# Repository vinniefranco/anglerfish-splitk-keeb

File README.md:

# Anglerfish Keyboard

Anglerfish, is a split keyboard with 3x5 column staggered keys, two thumb keys, and a trackball.

The Trackpoint can be placed on either side, and the PCB is a reversible design.

---

---

### Models
You can find all the step files for the case [here](assets/models)

### Electronic Components 
[Build of materials](assets/bom.md)

### Default Firmware Keymap

---

### Build Guide
Soon...

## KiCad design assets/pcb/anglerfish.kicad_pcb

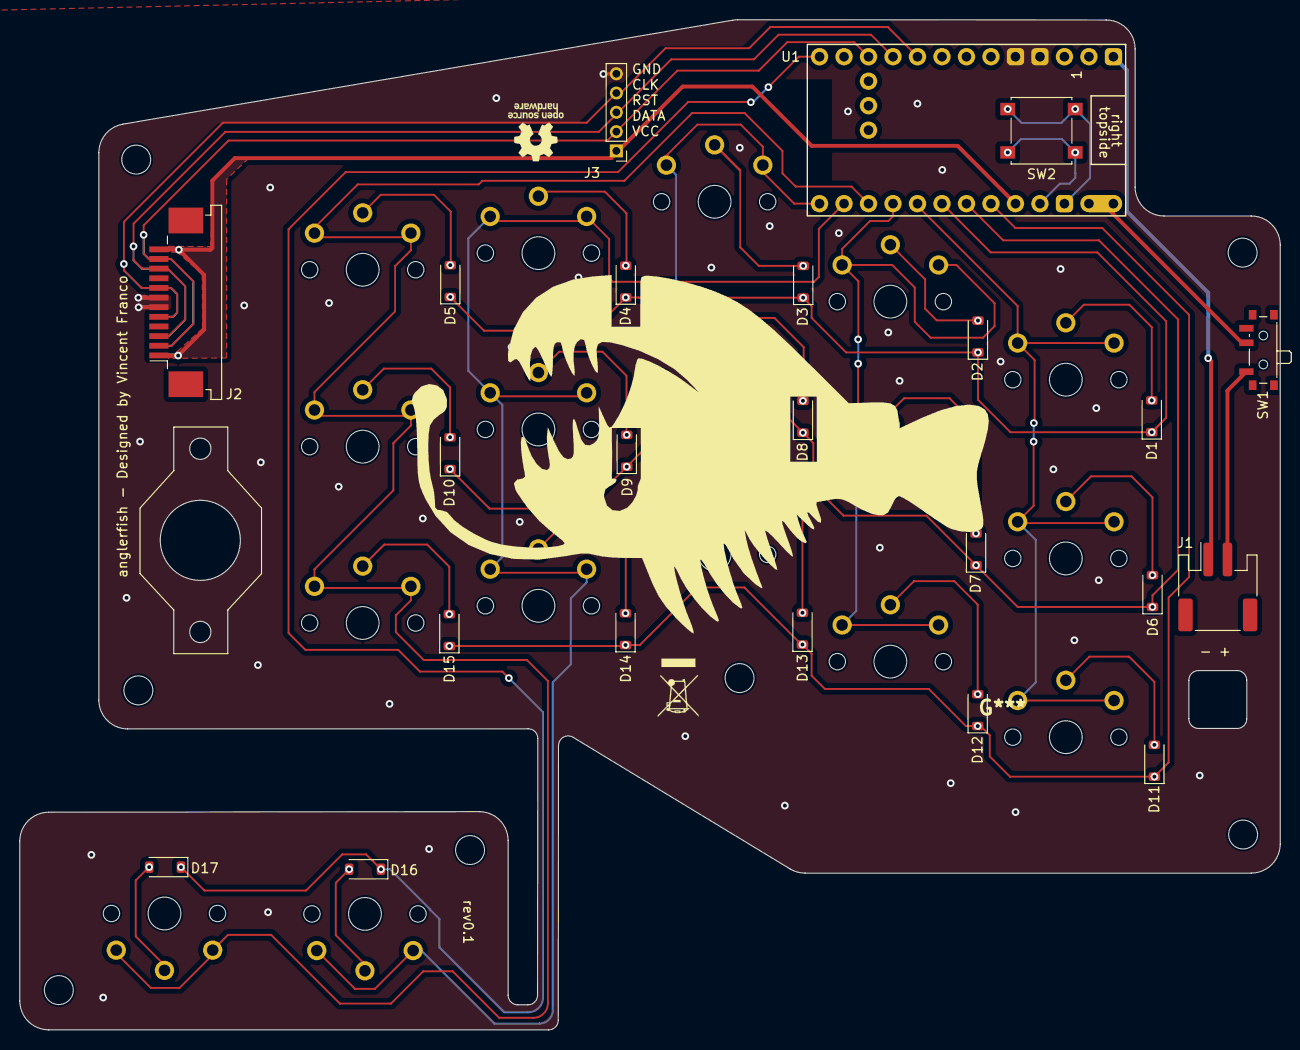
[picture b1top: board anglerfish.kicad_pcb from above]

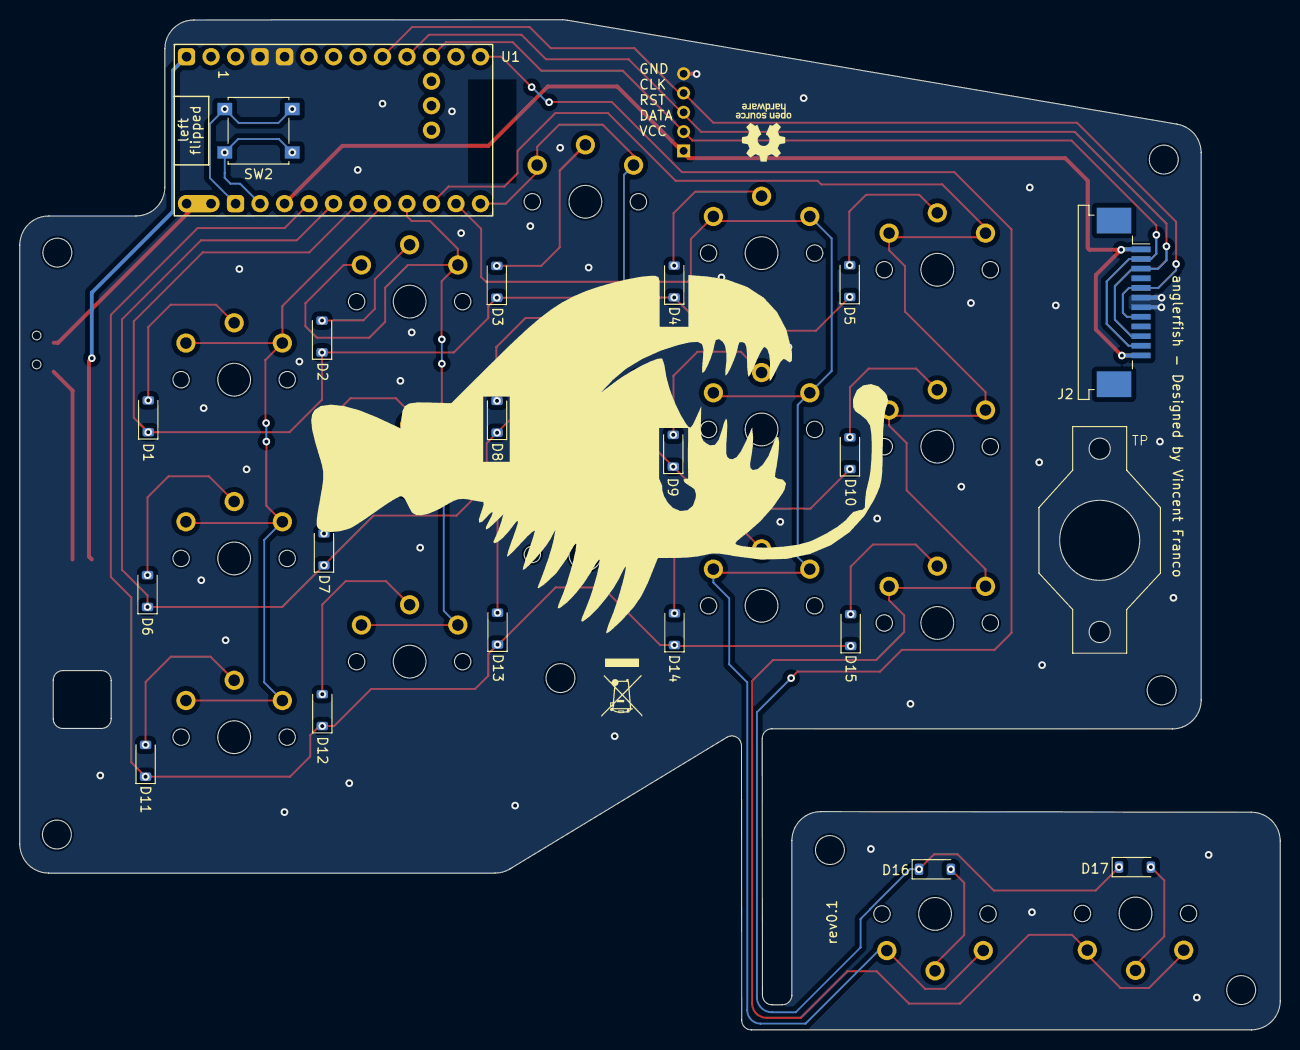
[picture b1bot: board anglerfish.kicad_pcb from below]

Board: 2 copper layers, 130.7 x 104.8 mm, 67 parts (19 on the bottom side), 35 nets.

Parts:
CH1, CH2, CH3, CH4, CH5, CH6, CH7, CH8, CH9, CH10, CH11, CH12, CH13, CH14, CH15, CH16, CH17: kailh choc; SW_choc_Reversible_1u
D1, D1#2, D2, D2#2, D3, D3#2, D4, D4#2, D5, D5#2, D6, D6#2, D7, D7#2, D8, D8#2, D9, D9#2, D10, D10#2, D11, D11#2, D12, D12#2, D13, D13#2, D14, D14#2, D15, D15#2, D16, D16#2, D17, D17#2: 1N4148; D_SOD-123
H1, H1#2, H2, H3, H4, H5, H6: MountingHole; MountingHole_3mm
J1: JST_PH_S2B-PH-SM4-TB; JST_PH_S2B-PH-SM4-TB_1x02-1MP_P2.00mm_Horizontal
J2, J2#2: TE_1-84952-2; TE_1-84952-2_1x12-1MP_P1.0mm_Horizontal
J3: Conn_01x05_Socket; PinHeader_1x05_P2.00mm_Vertical
SW1: SW_SPST_PCM12; SW_SPDT_PCM12
SW2, SW2#2: SW_SPST_B3S-1000
TP: Trackpoint
U1: supermini nrf / nice nano v2; nice_nano_AH_USBup

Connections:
BATTN: J1.1, U1.28 (GND)
BATTP: J1.2, SW1.1 (A), SW1.2 (B), U1.13 (BAT+), U1.29 (BAT+)
COL0: CH1.1, CH6.1, CH11.1, U1.20 (P1.15-LF)
COL1: CH2.1, CH7.1, CH12.1, U1.21 (P1.13-LF)
COL2: CH3.1, CH8.1, CH13.1, U1.24 (P0.09-LF)
COL3: CH4.1, CH9.1, CH14.1, CH16.1, U1.23 (P0-10-LF)
COL4: CH5.1, CH10.1, CH15.1, CH17.1, U1.22 (P1.11-LF)
unnamed: CH1.2, D1.2 (A), D1#2.2 (A)
unnamed: CH2.2, D2.2 (A), D2#2.2 (A)
unnamed: CH3.2, D3.2 (A), D3#2.2 (A)
unnamed: CH4.2, D4.2 (A), D4#2.2 (A)
unnamed: CH5.2, D5.2 (A), D5#2.2 (A)
unnamed: CH6.2, D6.2 (A), D6#2.2 (A)
unnamed: CH7.2, D7.2 (A), D7#2.2 (A)
unnamed: CH8.2, D8.2 (A), D8#2.2 (A)
unnamed: CH9.2, D9.2 (A), D9#2.2 (A)
unnamed: CH10.2, D10.2 (A), D10#2.2 (A)
unnamed: CH11.2, D11.2 (A), D11#2.2 (A)
unnamed: CH12.2, D12.2 (A), D12#2.2 (A)
unnamed: CH13.2, D13.2 (A), D13#2.2 (A)
unnamed: CH14.2, D14.2 (A), D14#2.2 (A)
unnamed: CH15.2, D15.2 (A), D15#2.2 (A)
unnamed: CH16.2, D16.2 (A), D16#2.2 (A)
unnamed: CH17.2, D17.2 (A), D17#2.2 (A)
ROW0: D1.1 (K), D1#2.1 (K), D2.1 (K), D2#2.1 (K), D3.1 (K), D3#2.1 (K), D4.1 (K), D4#2.1 (K), D5.1 (K), D5#2.1 (K), U1.19 (P0.02-LF)
ROW1: D6.1 (K), D6#2.1 (K), D7.1 (K), D7#2.1 (K), D8.1 (K), D8#2.1 (K), D9.1 (K), D9#2.1 (K), D10.1 (K), D10#2.1 (K), U1.18 (P0.29-LF)
ROW2: D11.1 (K), D11#2.1 (K), D12.1 (K), D12#2.1 (K), D13.1 (K), D13#2.1 (K), D14.1 (K), D14#2.1 (K), D15.1 (K), D15#2.1 (K), U1.17 (P0.31-LF)
ROW3: D16.1 (K), D16#2.1 (K), D17.1 (K), D17#2.1 (K), U1.12 (P1.06-LF)
RSTG: SW2.2 (B), SW2#2.2 (B), U1.14 (GND)
RSTR: SW2.1 (A), SW2#2.1 (A), U1.15 (RST)
TPCLK: J2.5, J2.8, J2#2.5, J2#2.8, J3.4, U1.8 (P0.24)
TPDATA: J2.2, J2.11, J2#2.2, J2#2.11, J3.2, U1.10 (P0.11)
TPGND: J2.6, J2.7, J2#2.6, J2#2.7, J3.5, U1.3 (GND), U1.4 (GND)
TPRST: J2.3, J2.10, J2#2.3, J2#2.10, J3.3, U1.9 (P1.00)
TPVCC: J2.1, J2.12, J2#2.1, J2#2.12, J3.1, U1.16 (3V3)

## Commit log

2024-03-25 fixup
2024-03-25 typo
2024-03-25 testing
2024-03-25 try enabling reset pin
2024-03-25 Disable some debug logging
2024-03-25 cleaning up keymap
2024-03-26 Adding keymap image/config
2024-03-27 flip-cols
2024-03-28 whoops
2024-03-28 now it flipped again
2024-03-28 maybe
2024-03-28 Double combo issue
2024-03-28 for realsies
2024-03-28 Better mapping
2024-03-28 Updating again
2024-03-28 Trackpoint adjustment keys
2024-03-28 Adding photos
2024-03-28 Readme work
2024-03-28 Adding models
2024-03-29 files
2024-03-29 Note
2024-03-29 Removing logging, capitalizing name
2024-04-10 Better keymap representation
2024-04-10 better formatting
2024-04-10 draw
2024-04-10 keymap-drawer render
2024-04-10 fixup?
2024-04-10 draw args
2024-04-10 I hate me
2024-04-10 naming
2024-04-10 kilme
2024-04-10 Trying info.json
2024-04-10 Update info.json to correct layout
2024-04-10 remove old keymap.svg
2024-04-10 Working on keymap
2024-04-10 remove ammend
2024-04-10 formatting
2024-04-10 Won't replace?
2024-04-26 Trying to deal with BT issues on NixOS
2024-05-22 Moving trackball code into place
2024-05-22 fixp
2024-05-28 Preparing firmware test
2024-05-28 Updated anglerfish.keymap
2024-05-28 Removing verbiage around PCB thickess
2024-05-28 Trackball > Trackpoint
2024-05-28 Attempt to add pin config for trackball
2024-05-28 Adding config
2024-05-28 Testing worked
2024-05-28 fix orientation
2024-05-28 almost
2024-05-28 closer-still
2024-05-28 whelp
2024-05-28 trying to improve performance
2024-05-28 Hopefully better trackingf
2024-05-28 testing-tweaks
2024-05-28 testing-again
2024-05-28 welp
2024-05-28 fixing typo
2024-05-28 automouse-layer
2024-05-28 cpi-work
2024-05-30 Cleanup
2024-05-30 Fix keymap
2024-05-30 back to 256 CPI
2024-06-10 Typo?
